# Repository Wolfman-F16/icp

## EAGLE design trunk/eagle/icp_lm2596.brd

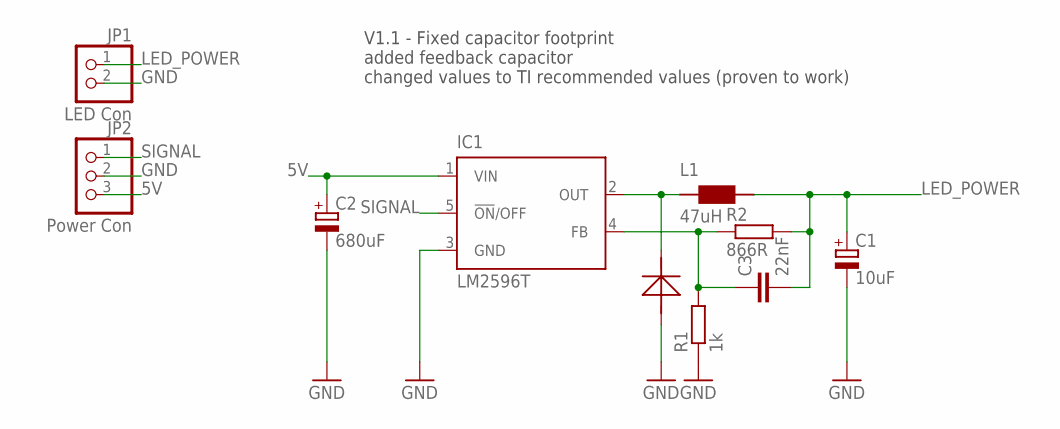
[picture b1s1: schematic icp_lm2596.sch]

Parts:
C1: 10uF; E2,5-7
C2: 680uF; E3,5-8
C3: 22nF; C0805
D1: SB 550; DO-201-6X
IC1: LM2596T; T05D
JP1: LED Con; 1X02
JP2: Power Con; 1X03
L1: 47uH; PISM
R1: 1k; 0207/2V
R2: 866R; 0207/2V

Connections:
5V: C2.+, IC1.1 (VIN), JP2.3
GND: C1.-, C2.-, D1.P$1 (A), IC1.3 (GND), JP1.2, JP2.2, R1.1
HOT: D1.P$2 (C), IC1.2 (OUT), L1.P$1
LED_POWER: C1.+, C3.2, JP1.1, L1.P$2, R2.2
unnamed: C3.1, IC1.4 (FB), R1.2, R2.1
SIGNAL: IC1.5 (!ON!/OFF), JP2.1

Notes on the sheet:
V1.1 - Fixed capacitor footprint added feedback capacitor changed values to TI recommended values (proven to work)

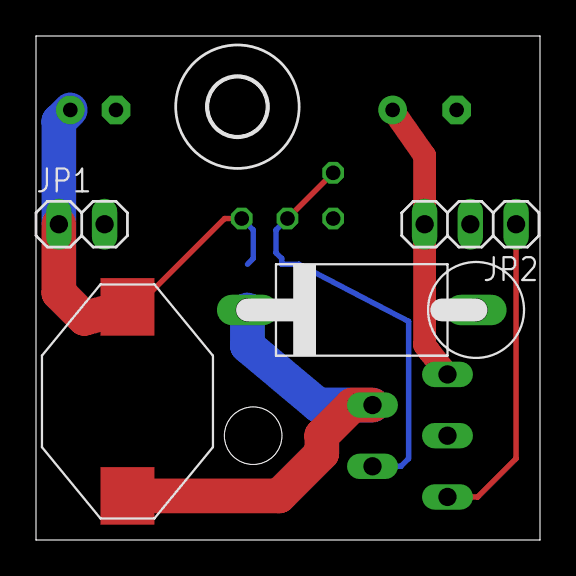
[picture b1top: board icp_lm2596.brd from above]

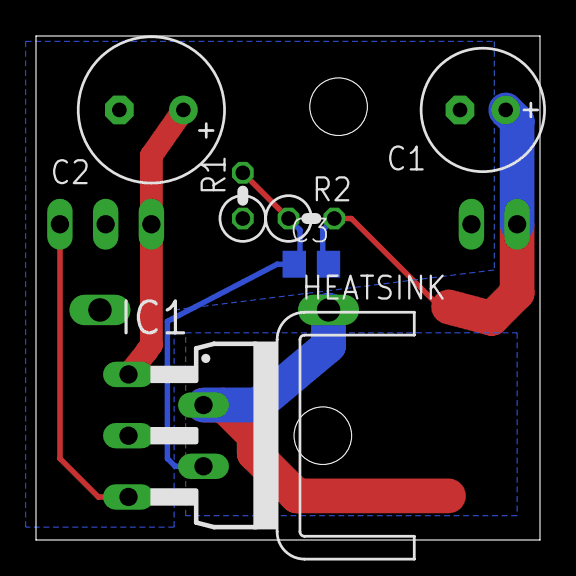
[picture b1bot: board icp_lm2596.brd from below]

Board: 2 copper layers, 28.0 x 28.0 mm, 12 parts (7 on the bottom side), 6 nets.

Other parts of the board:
HEATSINK: D03S
U$1: 3,2

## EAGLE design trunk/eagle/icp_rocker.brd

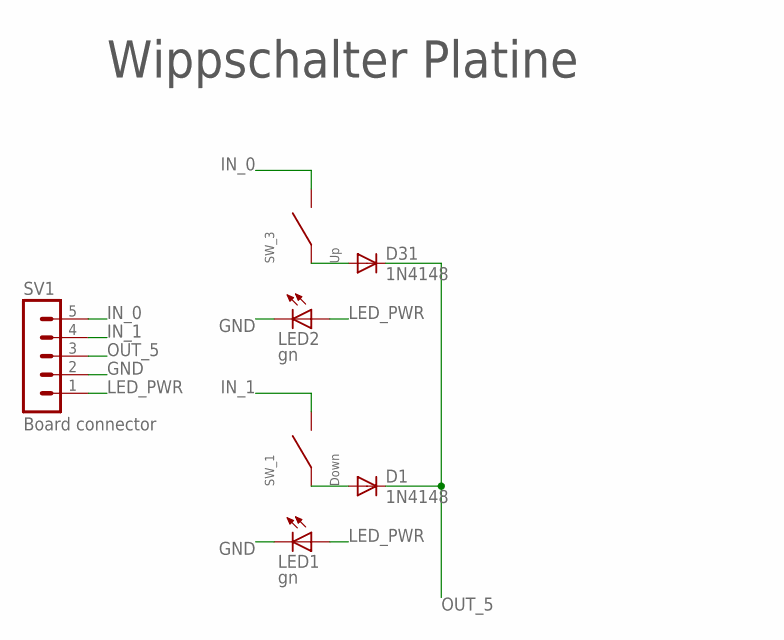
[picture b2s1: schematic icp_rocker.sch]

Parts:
D1, D31: 1N4148; DO35-10
LED1, LED2: gn; CHIPLED_1206
SV1: Board connector; MA05-1
SW_1: Down; TYPE_A
SW_3: Up; TYPE_A

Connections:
GND: LED1.C, LED2.C, SV1.2
IN_0: SV1.5, SW_3.P$1
IN_1: SV1.4, SW_1.P$1
LED_PWR: LED1.A, LED2.A, SV1.1
unnamed: D1.A, SW_1.P$2
unnamed: D31.A, SW_3.P$2
OUT_5: D1.C, D31.C, SV1.3

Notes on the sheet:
Wippschalter Platine

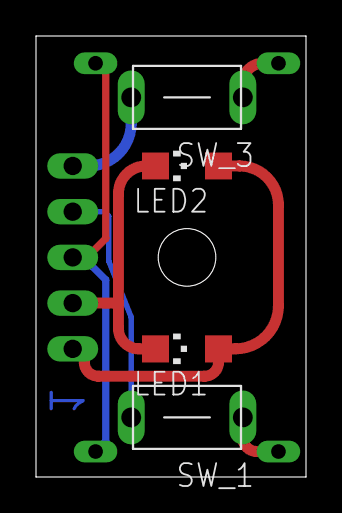
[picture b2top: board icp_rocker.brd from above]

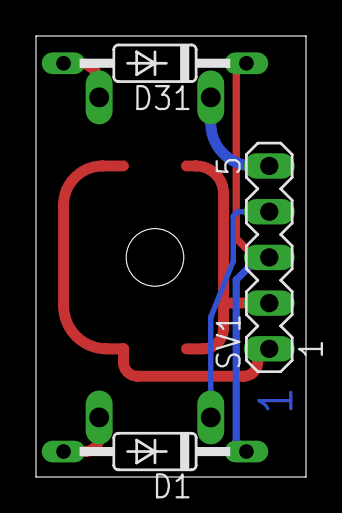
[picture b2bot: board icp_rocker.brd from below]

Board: 2 copper layers, 15.0 x 24.5 mm, 7 parts (3 on the bottom side), 7 nets.

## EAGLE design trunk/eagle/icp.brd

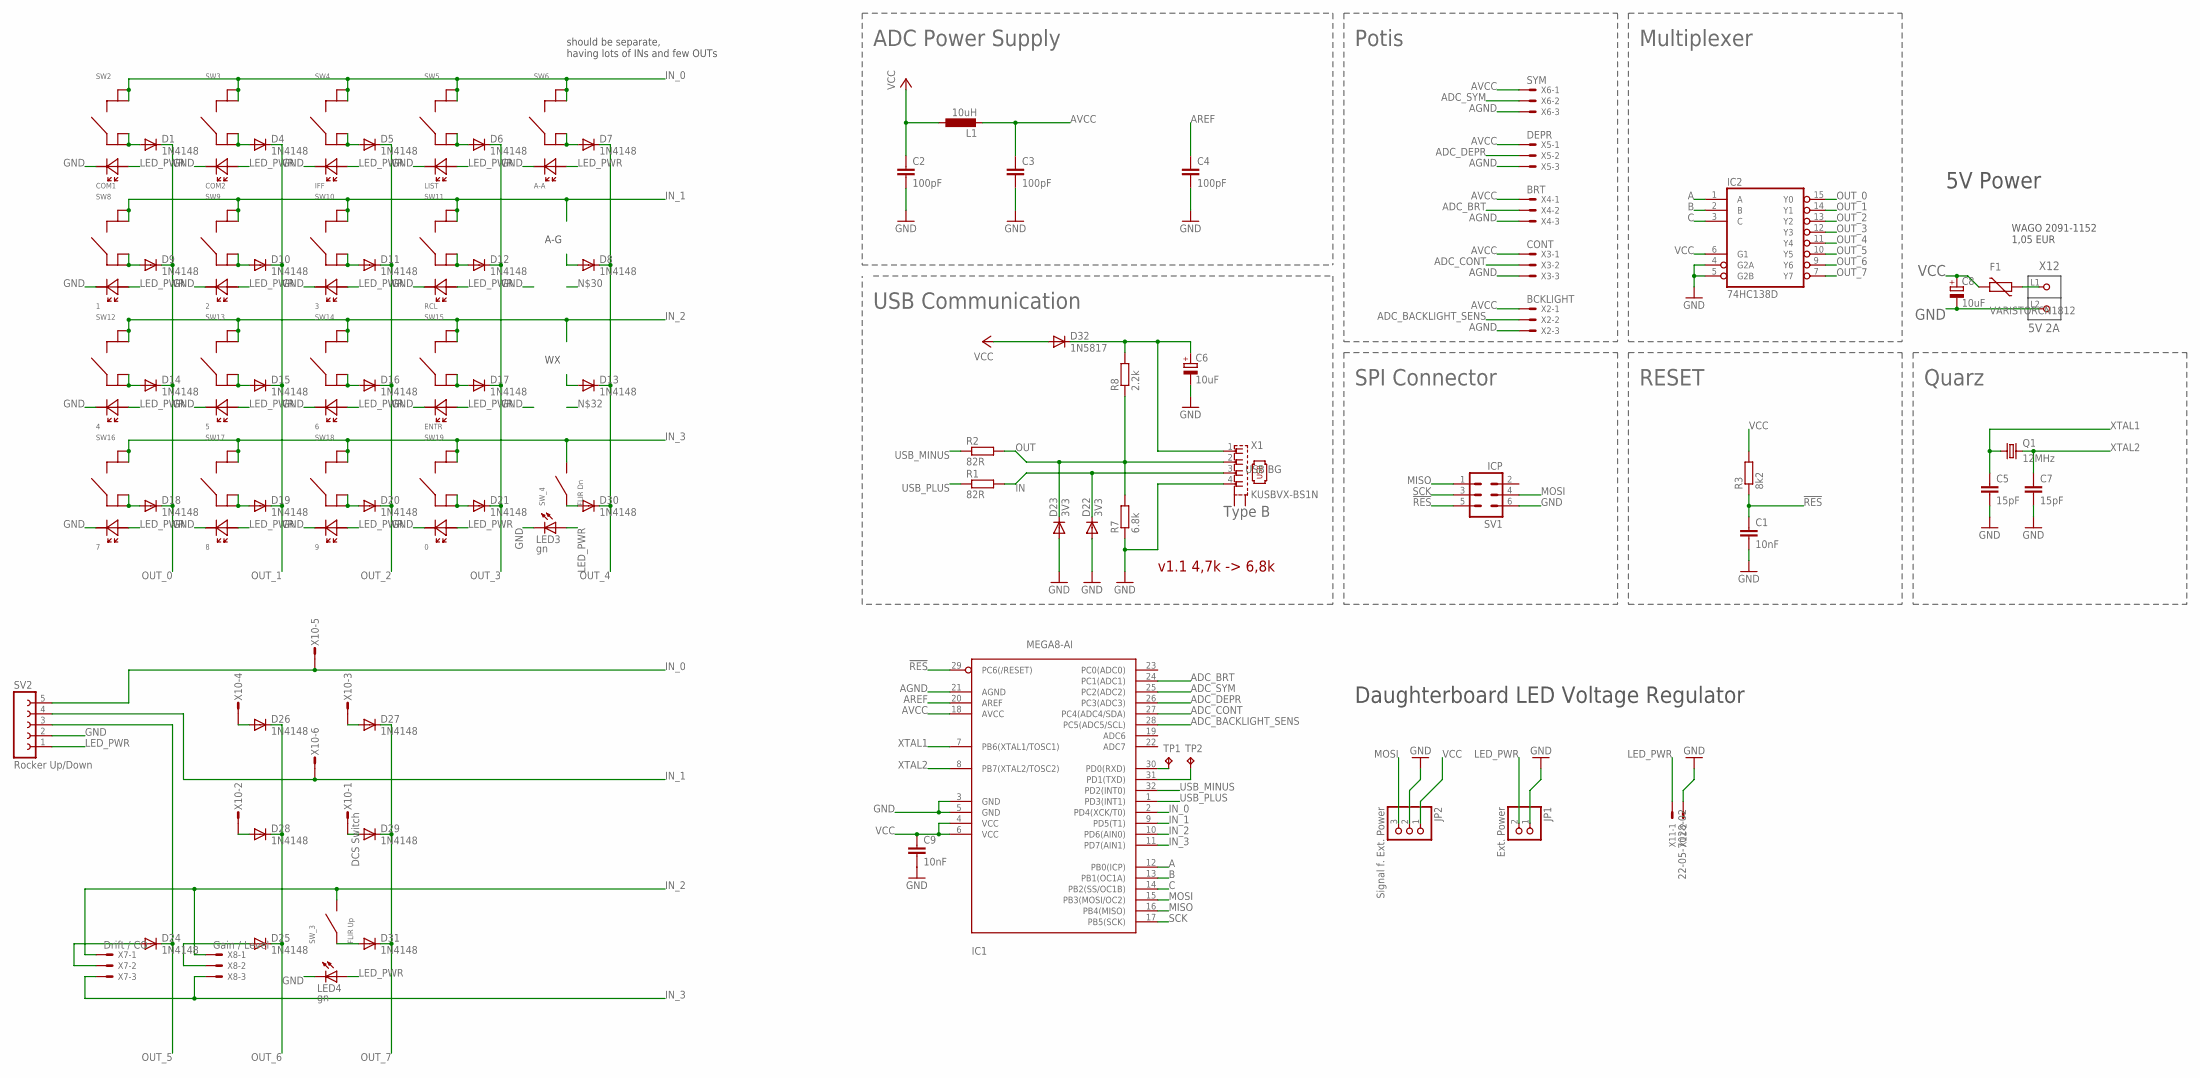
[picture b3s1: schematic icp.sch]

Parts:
C1, C9: 10nF; C1206
C2, C3, C4: 100pF; C0805
C5, C7: 15pF; C0805
C6, C8: 10uF; E2-5
D1, D4, D5, D6, D7, D8, D9, D10, D11, D12, D13, D14, D15, D16, D17, D18, D19, D20, D21, D24, D25, D26, D27, D28, D29, D30, D31: 1N4148; DO35-10
D22, D23: 3V3; D-5
D32: 1N5817; DO35-10
F1: VARISTORCN1812; CT/CN1812
IC1: MEGA8-AI; TQFP32-08
IC2: 74HC138D; SO16
JP1: Ext. Power; 1X02
JP2: Signal f. Ext. Power; 1X03
L1: 10uH; 0207/15
LED3, LED4: gn; CHIPLED_1206
Q1: 12MHz; HC49U-V
R1, R2: 82R; R0805W
R3: 8k2; R0805
R7: 6.8k; 0207/5V
R8: 2.2k; R0805
SV1: ICP; MA03-2
SV2: Rocker Up/Down; FE05-1
SW2: COM1; 3FTL620
SW3: COM2; 3FTL620
SW4: IFF; 3FTL620
SW5: LIST; 3FTL620
SW6: A-A; 3FTL620
SW8: 1; 3FTL620
SW9: 2; 3FTL620
SW10: 3; 3FTL620
SW11: RCL; 3FTL620
SW12: 4; 3FTL620
SW13: 5; 3FTL620
SW14: 6; 3FTL620
SW15: ENTR; 3FTL620
SW16: 7; 3FTL620
SW17: 8; 3FTL620
SW18: 9; 3FTL620
SW19: 0; 3FTL620
SW_3: FLIR Up; TYPE_A
SW_4: FLIR Dn; TYPE_A
TP1, TP2: TPTP06SQ; TP06SQ
X1: KUSBVX-BS1N
X2: BCKLIGHT; 22-23-2031
X3: CONT; 22-23-2031
X4: BRT; 22-23-2031
X5: DEPR; 22-23-2031
X6: SYM; 22-23-2031
X7: Drift / CO; 22-23-2031; MPN 22-23-2031
X8: Gain / Level; 22-23-2031; MPN 22-23-2031
X10: DCS Switch; MICROMATCH-6
X11: 22-05-7028-02; 7395-02
X12: 5V 2A; P-2091-1152

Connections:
!RES: C1.1, IC1.29 (PC6(/RESET)), R3.1, SV1.5
A: IC1.12 (PB0(ICP)), IC2.1 (A)
ADC_BACKLIGHT_SENS: IC1.28 (PC5(ADC5/SCL)), X2.2
ADC_BRT: IC1.24 (PC1(ADC1)), X4.2
ADC_CONT: IC1.27 (PC4(ADC4/SDA)), X3.2
ADC_DEPR: IC1.26 (PC3(ADC3)), X5.2
ADC_SYM: IC1.25 (PC2(ADC2)), X6.2
AGND: IC1.21 (AGND), X2.3, X3.3, X4.3, X5.3, X6.3
AREF: C4.1, IC1.20 (AREF)
AVCC: C3.1, IC1.18 (AVCC), L1.2, X2.1, X3.1, X4.1, X5.1, X6.1
B: IC1.13 (PB1(OC1A)), IC2.2 (B)
C: IC1.14 (PB2(SS/OC1B)), IC2.3 (C)
GND: C1.2, C2.2, C3.2, C4.2, C5.2, C6.-, C7.2, C8.-, C9.2, D22.A, D23.A, IC1.3 (GND), IC1.5 (GND), IC2.4 (G2A), IC2.5 (G2B), IC2.8 (GND), JP1.1, JP2.2, LED3.C, LED4.C, R7.1, SV1.6, SV2.2, SW2.P$6 (LED$4), SW3.P$6 (LED$4), SW4.P$6 (LED$4), SW5.P$6 (LED$4), SW6.P$6 (LED$4), SW8.P$6 (LED$4), SW9.P$6 (LED$4), SW10.P$6 (LED$4), SW11.P$6 (LED$4), SW12.P$6 (LED$4), SW13.P$6 (LED$4), SW14.P$6 (LED$4), SW15.P$6 (LED$4), SW16.P$6 (LED$4), SW17.P$6 (LED$4), SW18.P$6 (LED$4), SW19.P$6 (LED$4), X1.4, X11.2, X12.L2 (P2)
IN: D22.C, R1.2, X1.3
IN_0: IC1.2 (PD4(XCK/T0)), SV2.5, SW2.P$1, SW2.P$3, SW3.P$1, SW3.P$3, SW4.P$1, SW4.P$3, SW5.P$1, SW5.P$3, SW6.P$1, SW6.P$3, X10.5
IN_1: IC1.9 (PD5(T1)), SV2.4, SW8.P$1, SW8.P$3, SW9.P$1, SW9.P$3, SW10.P$1, SW10.P$3, SW11.P$1, SW11.P$3, X10.6
IN_2: IC1.10 (PD6(AIN0)), SW12.P$1, SW12.P$3, SW13.P$1, SW13.P$3, SW14.P$1, SW14.P$3, SW15.P$1, SW15.P$3, SW_3.P$1, X7.1, X8.1
IN_3: IC1.11 (PD7(AIN1)), SW16.P$1, SW16.P$3, SW17.P$1, SW17.P$3, SW18.P$1, SW18.P$3, SW19.P$1, SW19.P$3, SW_4.P$1, X7.3, X8.3
LED_PWR: JP1.2, LED3.A, LED4.A, SV2.1, SW2.P$5 (LED$3), SW3.P$5 (LED$3), SW4.P$5 (LED$3), SW5.P$5 (LED$3), SW6.P$5 (LED$3), SW8.P$5 (LED$3), SW9.P$5 (LED$3), SW10.P$5 (LED$3), SW11.P$5 (LED$3), SW12.P$5 (LED$3), SW13.P$5 (LED$3), SW14.P$5 (LED$3), SW15.P$5 (LED$3), SW16.P$5 (LED$3), SW17.P$5 (LED$3), SW18.P$5 (LED$3), SW19.P$5 (LED$3), X11.1
MISO: IC1.16 (PB4(MISO)), SV1.1
MOSI: IC1.15 (PB3(MOSI/OC2)), JP2.3, SV1.4
unnamed: C6.+, D32.C, R8.2, X1.1
unnamed: D7.A, SW6.P$2, SW6.P$4
unnamed: D30.A, SW_4.P$2
unnamed: F1.1, X12.L1 (P1)
unnamed: D31.A, SW_3.P$2
unnamed: D24.A, X7.2
unnamed: D25.A, X8.2
unnamed: D26.A, X10.4
unnamed: D28.A, X10.2
unnamed: D27.A, X10.3
unnamed: D1.A, SW2.P$2, SW2.P$4
unnamed: D9.A, SW8.P$2, SW8.P$4
unnamed: D4.A, SW3.P$2, SW3.P$4
unnamed: D5.A, SW4.P$2, SW4.P$4
unnamed: D6.A, SW5.P$2, SW5.P$4
unnamed: D12.A, SW11.P$2, SW11.P$4
unnamed: D11.A, SW10.P$2, SW10.P$4
unnamed: D10.A, SW9.P$2, SW9.P$4
unnamed: D14.A, SW12.P$2, SW12.P$4
unnamed: D15.A, SW13.P$2, SW13.P$4
unnamed: D16.A, SW14.P$2, SW14.P$4
unnamed: D17.A, SW15.P$2, SW15.P$4
unnamed: D18.A, SW16.P$2, SW16.P$4
unnamed: D19.A, SW17.P$2, SW17.P$4
unnamed: D20.A, SW18.P$2, SW18.P$4
unnamed: D21.A, SW19.P$2, SW19.P$4
unnamed: D29.A, X10.1
OUT: D23.C, R2.2, R7.2, R8.1, X1.2
OUT_0: D1.C, D9.C, D14.C, D18.C, IC2.15 (Y0)
OUT_1: D4.C, D10.C, D15.C, D19.C, IC2.14 (Y1)
OUT_2: D5.C, D11.C, D16.C, D20.C, IC2.13 (Y2)
OUT_3: D6.C, D12.C, D17.C, D21.C, IC2.12 (Y3)
OUT_4: D7.C, D8.C, D13.C, D30.C, IC2.11 (Y4)
OUT_5: D24.C, IC2.10 (Y5), SV2.3
OUT_6: D25.C, D26.C, D28.C, IC2.9 (Y6)
OUT_7: D27.C, D29.C, D31.C, IC2.7 (Y7)
RX: IC1.30 (PD0(RXD)), TP1.TP
SCK: IC1.17 (PB5(SCK)), SV1.3
TX: IC1.31 (PD1(TXD)), TP2.TP
USB_MINUS: IC1.32 (PD2(INT0)), R2.1
USB_PLUS: IC1.1 (PD3(INT1)), R1.1
VCC: C2.1, C8.+, C9.1, D32.A, F1.2, IC1.4 (VCC), IC1.6 (VCC), IC2.6 (G1), IC2.16 (VCC), JP2.1, L1.1, R3.2
XTAL1: C5.1, IC1.7 (PB6(XTAL1/TOSC1)), Q1.1
XTAL2: C7.1, IC1.8 (PB7(XTAL2/TOSC2)), Q1.2

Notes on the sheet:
USB Communication
Type B
should be separate, having lots of INs and few OUTs
SPI Connector
RESET
ADC Power Supply
Potis
Quarz
Multiplexer
5V Power
A-G
Daughterboard LED Voltage Regulator
WAGO 2091-1152 1,05 EUR
v1.1 4,7k -> 6,8k

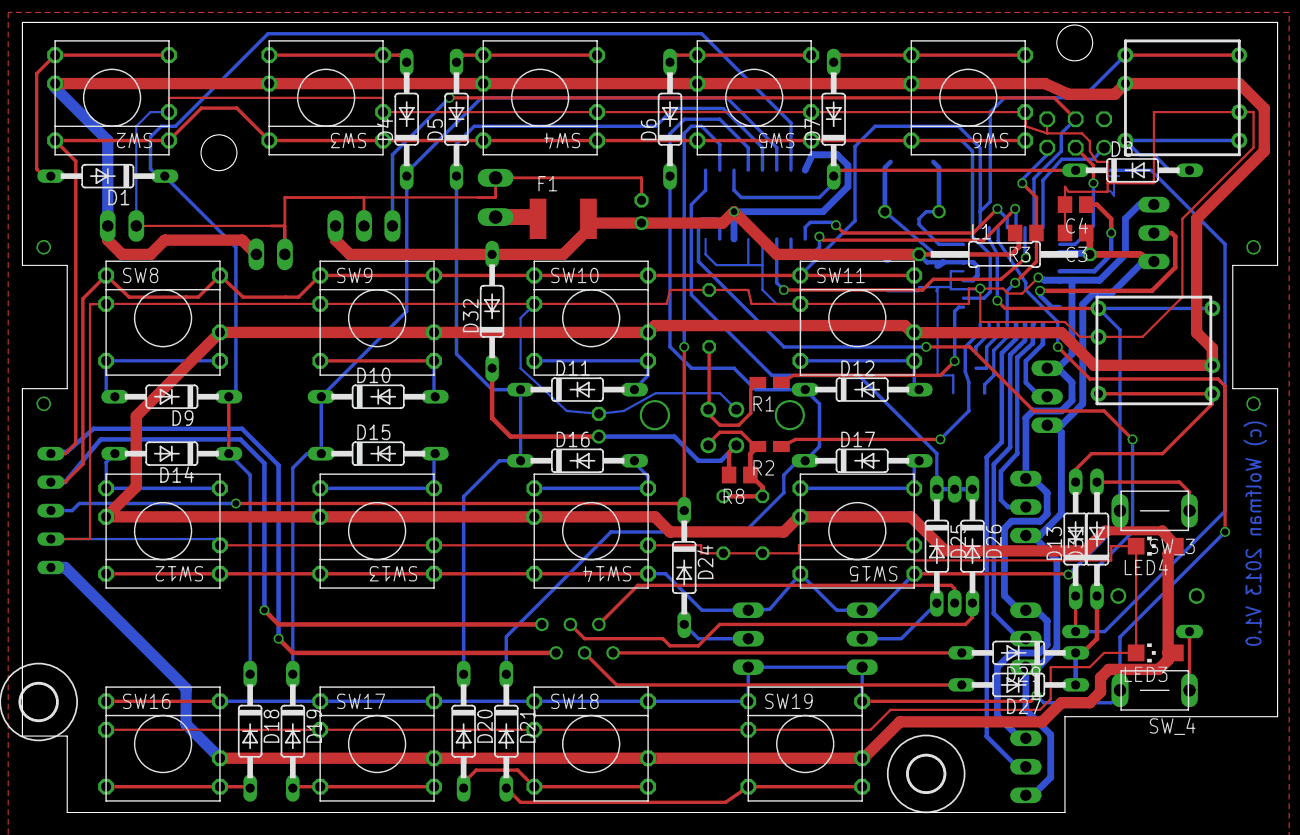
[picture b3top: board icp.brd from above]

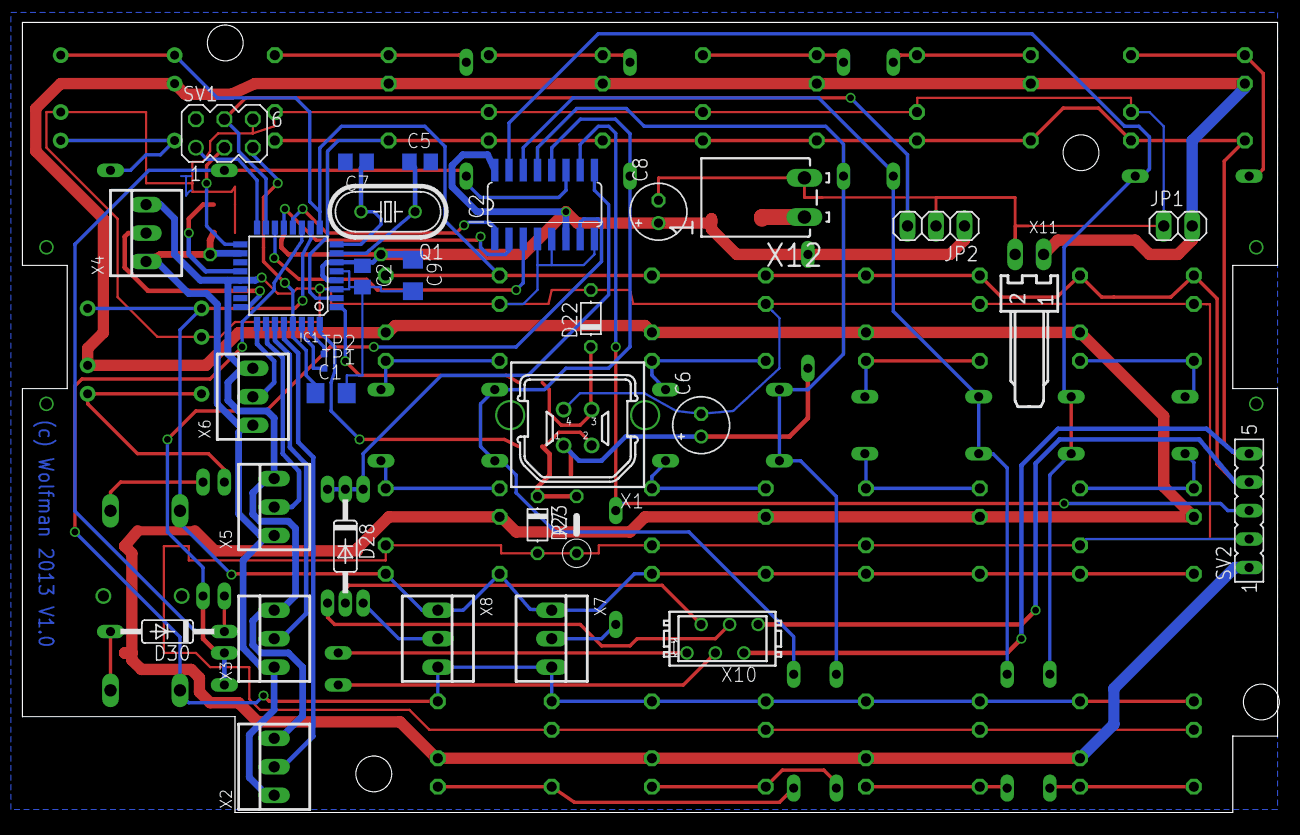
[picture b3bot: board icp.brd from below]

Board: 2 copper layers, 112.0 x 70.5 mm, 89 parts (32 on the bottom side), 65 nets.

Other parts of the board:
U$5, U$7: 3,2

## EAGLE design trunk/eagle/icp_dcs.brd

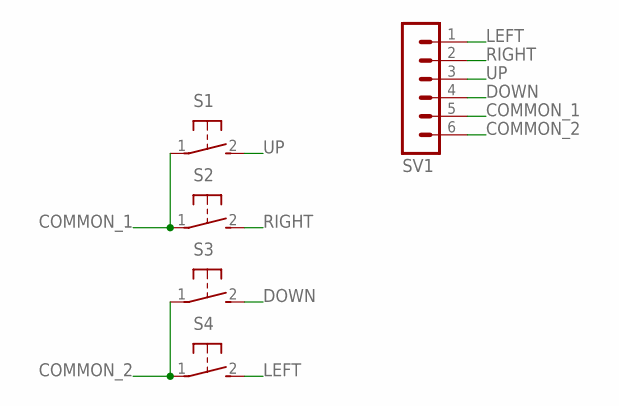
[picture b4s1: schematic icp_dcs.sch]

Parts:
S1, S2, S3, S4: 31-XX; B3F-31XX
SV1: MA06-1

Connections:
COMMON_1: S1.1, S2.1, SV1.5
COMMON_2: S3.1, S4.1, SV1.6
DOWN: S3.2 (S), SV1.4
LEFT: S4.2 (S), SV1.1
RIGHT: S2.2 (S), SV1.2
UP: S1.2 (S), SV1.3

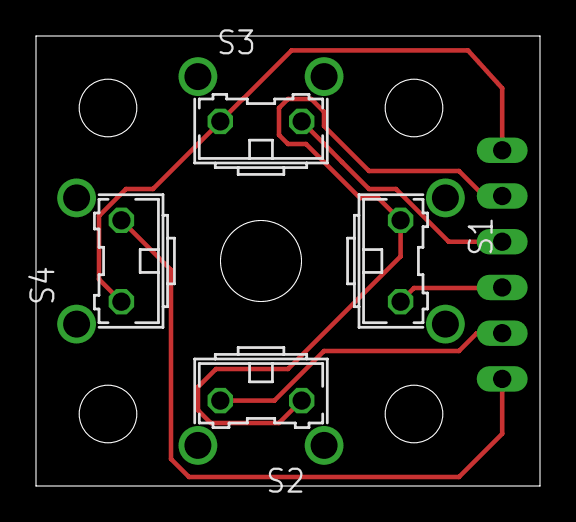
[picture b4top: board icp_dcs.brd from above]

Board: 2 copper layers, 28.0 x 25.0 mm, 5 parts (1 on the bottom side), 6 nets.

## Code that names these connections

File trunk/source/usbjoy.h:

/*
 * usbjoy.h
 *
 * Copyright: (c) 2012 by Wolfgang Engelhard
 * License: GNU GPL v2 (see License.txt)
 */

#ifndef USBJOY_H_
#define USBJOY_H_

#include <inttypes.h>

/****************************   DEFINITIONS         **************************/
#define USB_INT         	PD3

#define SPI_MOSI        	PB3
#define SPI_MISO        	PB4
#define SPI_SCK         	PB5

#define MUX_A 				PB0
#define MUX_B   			PB1
#define MUX_C  				PB2

#define PWM                 PB3

#define TX                  PD1

// PORT C is input for ADC

// PORT D is input for Keys and has USB interrupt, Pin7 is output

#define NR_OF_AXIS 	5

/****************************   ENUMS & STRUCTS     **************************/
typedef struct {
	unsigned dataRdy:1;
	unsigned adcChn:3;
	unsigned tmrRdy:1;
	unsigned usbRdy:1;
	unsigned brtCtl:1;
	unsigned symOff:1;
} flags_t;

/****************************   GLOBAL VARIABLES    **************************/
flags_t flags;
uint8_t axis[NR_OF_AXIS];
uint8_t btns[8];

/****************************   FUNCTION DECLARATIONS ************************/
void 		initIO(void);
void 		getAdcData(void);
uint8_t     getBtnData(void);
void        processSymOn(void);

#endif /* USBJOY_H_ */

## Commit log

2014-03-20 update comments for GPLv2 license added necessary files for license
2014-12-21 added libraries (incl. headers) AVR_ADC AVR_TIMER (probably requires correction of library paths in ICP project)
2015-08-23 Migrating wiki contents from Google Code
